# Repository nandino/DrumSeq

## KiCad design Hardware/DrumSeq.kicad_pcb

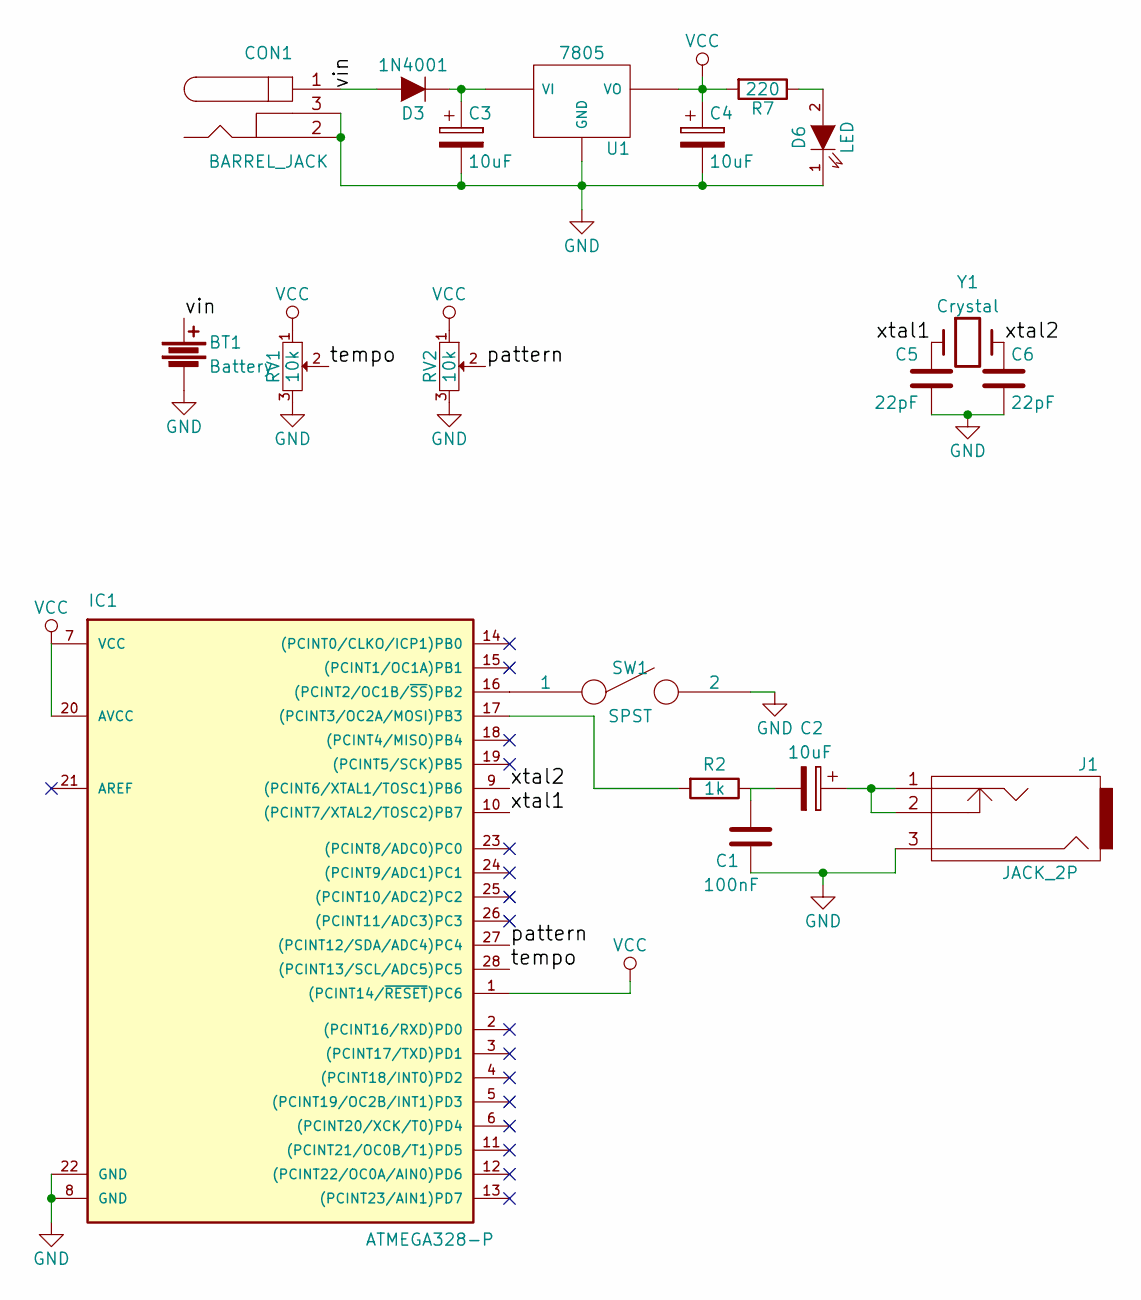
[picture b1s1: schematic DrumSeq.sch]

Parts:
BT1: Battery; PINHEAD1-2
C1: 100nF; C_Disc_D3_P2.5
C2, C3, C4: 10uF; C_Radial_D5_L6_P2.5
C5, C6: 22pF; C_Disc_D3_P2.5
CON1: BARREL_JACK; JACK_ALIM
D3: 1N4001; Diode_DO-35_SOD27_Horizontal_RM10
D6: LED; LED-5MM
IC1: ATMEGA328-P; DIP-28_W7.62mm_LongPads
J1: JACK_2P; PINHEAD1-3
R2: 1k; Resistor_Horizontal_RM10mm
R7: 220; Resistor_Horizontal_RM10mm
RV1, RV2: 10k; Potentiometer_Alps-RK16-single
SW1: SPST; Pin_Header_Straight_1x02
U1: 7805; TO-220_Neutral123_Vertical
Y1: Crystal; Crystal_HC48-U_Vertical

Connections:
/pattern: IC1.27 ((PCINT12/SDA/ADC4)PC4), RV2.2
/tempo: IC1.28 ((PCINT13/SCL/ADC5)PC5), RV1.2
/vin: BT1.1, CON1.1, D3.2 (A)
/xtal1: C5.2, IC1.10 ((PCINT7/XTAL2/TOSC2)PB7), Y1.1
/xtal2: C6.1, IC1.9 ((PCINT6/XTAL1/TOSC1)PB6), Y1.2
GND: BT1.2, C1.2, C3.2, C4.2, C5.1, C6.2, CON1.2, CON1.3, D6.1 (K), IC1.8 (GND), IC1.22 (GND), J1.3, RV1.3, RV2.3, SW1.2, U1.2 (GND)
unnamed: C1.1, C2.2, R2.1
unnamed: C2.1, J1.1, J1.2
unnamed: C3.1, D3.1 (K), U1.1 (VI)
unnamed: D6.2 (A), R7.1
unnamed: IC1.16 ((PCINT2/OC1B/~SS~)PB2), SW1.1
unnamed: IC1.17 ((PCINT3/OC2A/MOSI)PB3), R2.2
VCC: C4.1, IC1.1 ((PCINT14/~RESET~)PC6), IC1.7 (VCC), IC1.20 (AVCC), R7.2, RV1.1, RV2.1, U1.3 (VO)

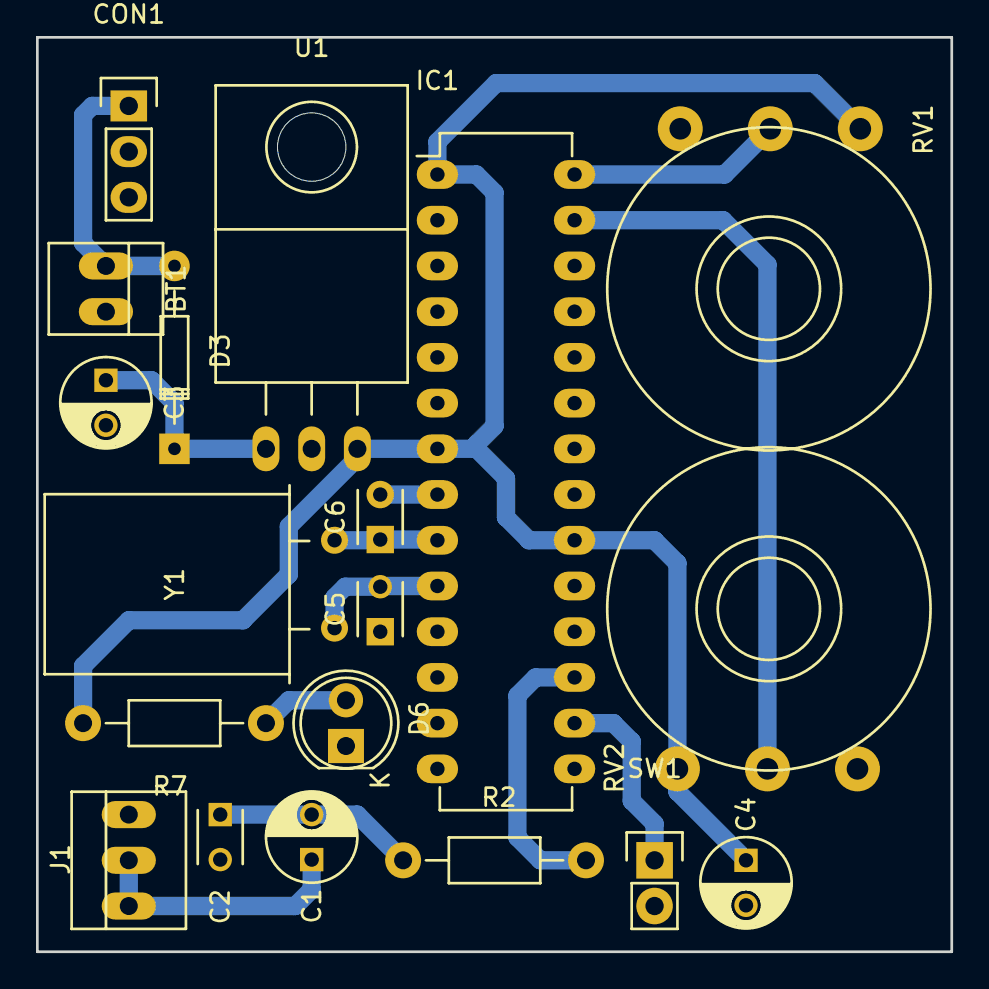
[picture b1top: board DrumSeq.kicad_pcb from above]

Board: 2 copper layers, 50.8 x 50.8 mm, 19 parts (0 on the bottom side), 13 nets.

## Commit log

2017-10-10 ejercicio para Varguardia Sur
2017-10-10 Agrego carpetas Hardware y Firmware
